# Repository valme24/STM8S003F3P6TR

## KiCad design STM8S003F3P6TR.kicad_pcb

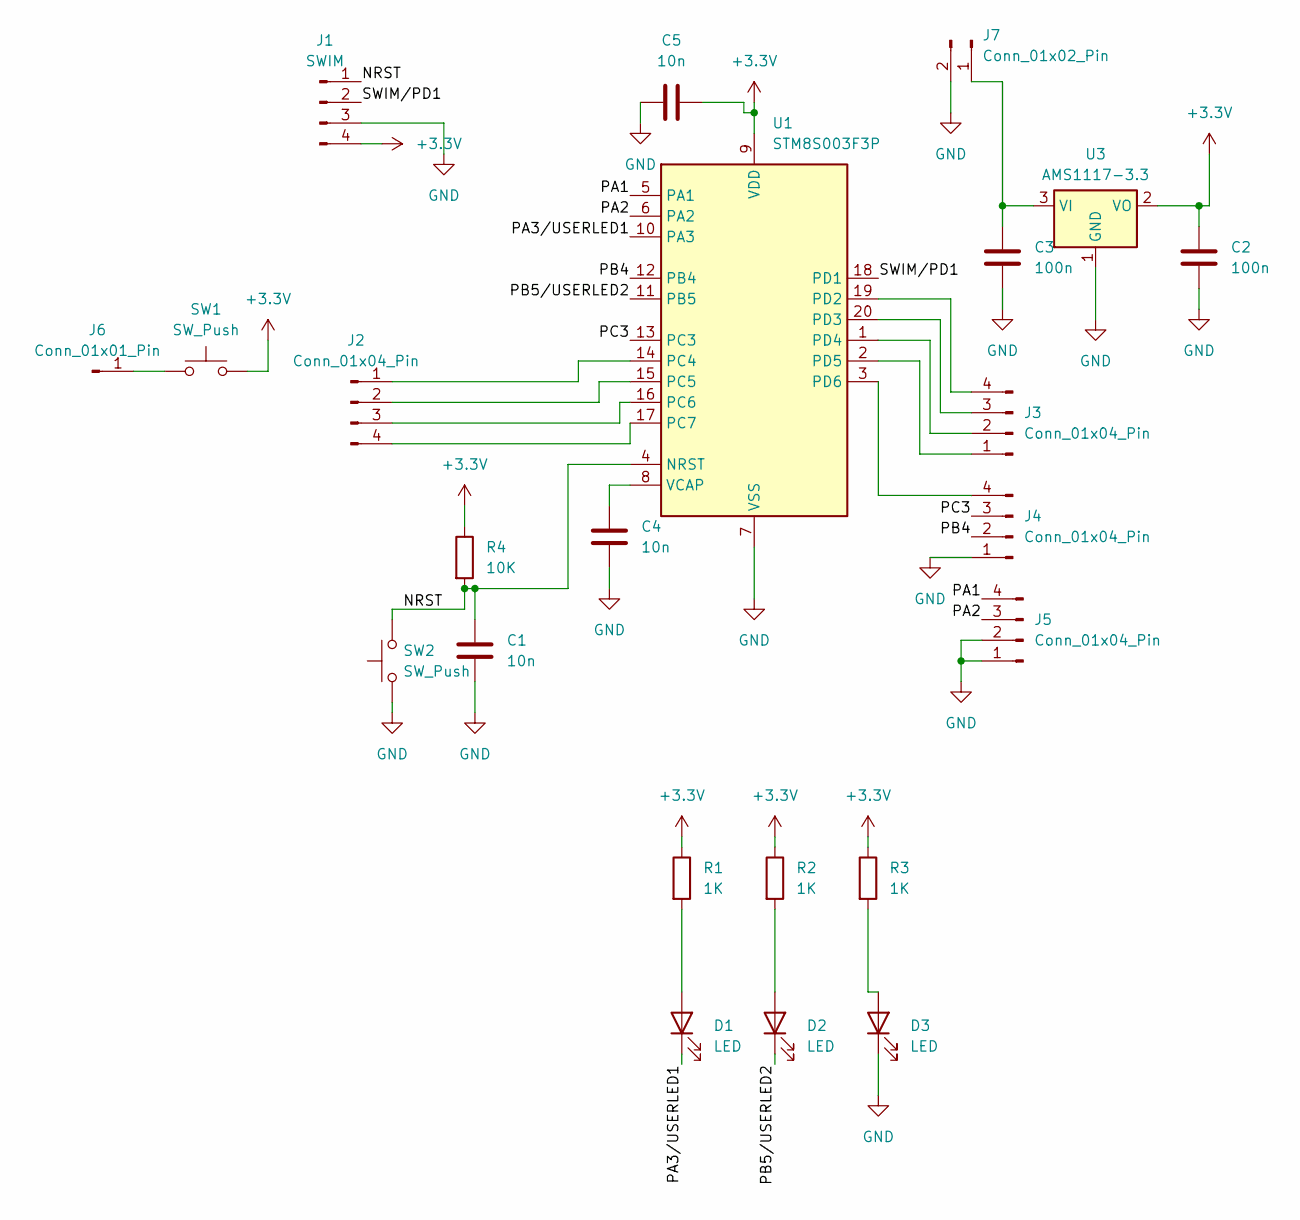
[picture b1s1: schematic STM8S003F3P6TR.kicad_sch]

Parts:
C1, C4, C5: 10n; C_0805_2012Metric
C2, C3: 100n; C_0805_2012Metric
D1, D2, D3: LED; LED_D3.0mm
J1: SWIM; PinHeader_1x04_P2.54mm_Vertical
J2, J3, J4, J5: Conn_01x04_Pin; PinHeader_1x04_P2.54mm_Vertical
J6: Conn_01x01_Pin; PinSocket_1x01_P2.54mm_Vertical
J7: Conn_01x02_Pin; CONN
R1, R2, R3: 1K; C_0603_1608Metric
R4: 10K; C_0603_1608Metric
SW1, SW2: SW_Push; SW_PUSH-12mm
U1: STM8S003F3P; TSSOP-20_4.4x6.5mm_P0.65mm
U3: AMS1117-3.3; SOT-223-3_TabPin2

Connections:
+3.3V: C2.1, C5.2, J1.4, R1.1, R2.1, R3.1, R4.1, SW1.2, U1.9 (VDD), U3.2 (VO); also elsewhere on the board
/NRST: C1.1, J1.1, R4.2, SW2.2, U1.4 (NRST); also elsewhere on the board
/PA1: J5.4, U1.5 (PA1)
/PA2: J5.3, U1.6 (PA2)
/PA3/USERLED1: D1.1 (K), U1.10 (PA3)
/PB4: J4.2, U1.12 (PB4)
/PB5/USERLED2: D2.1 (K), U1.11 (PB5)
/PC3: J4.3, U1.13 (PC3)
/SWIM/PD1: J1.2, U1.18 (PD1); also elsewhere on the board
GND: C1.2, C2.2, C3.2, C4.2, C5.1, D3.1 (K), J1.3, J4.1, J5.1, J5.2, J7.2, SW2.1, U1.7 (VSS), U3.1 (GND); also elsewhere on the board
unnamed: D1.2 (A), R1.2
unnamed: D2.2 (A), R2.2
unnamed: D3.2 (A), R3.2
unnamed: J2.1, U1.14 (PC4)
unnamed: J2.2, U1.15 (PC5)
unnamed: J2.3, U1.16 (PC6)
unnamed: J2.4, U1.17 (PC7)
unnamed: J3.1, U1.2 (PD5)
unnamed: J3.2, U1.1 (PD4)
unnamed: J3.3, U1.20 (PD3)
unnamed: J3.4, U1.19 (PD2)
unnamed: J4.4, U1.3 (PD6)
unnamed: J6.1 (Pin_1_1), SW1.1
unnamed: C3.1, J7.1, U3.3 (VI)
unnamed: C4.1, U1.8 (VCAP)

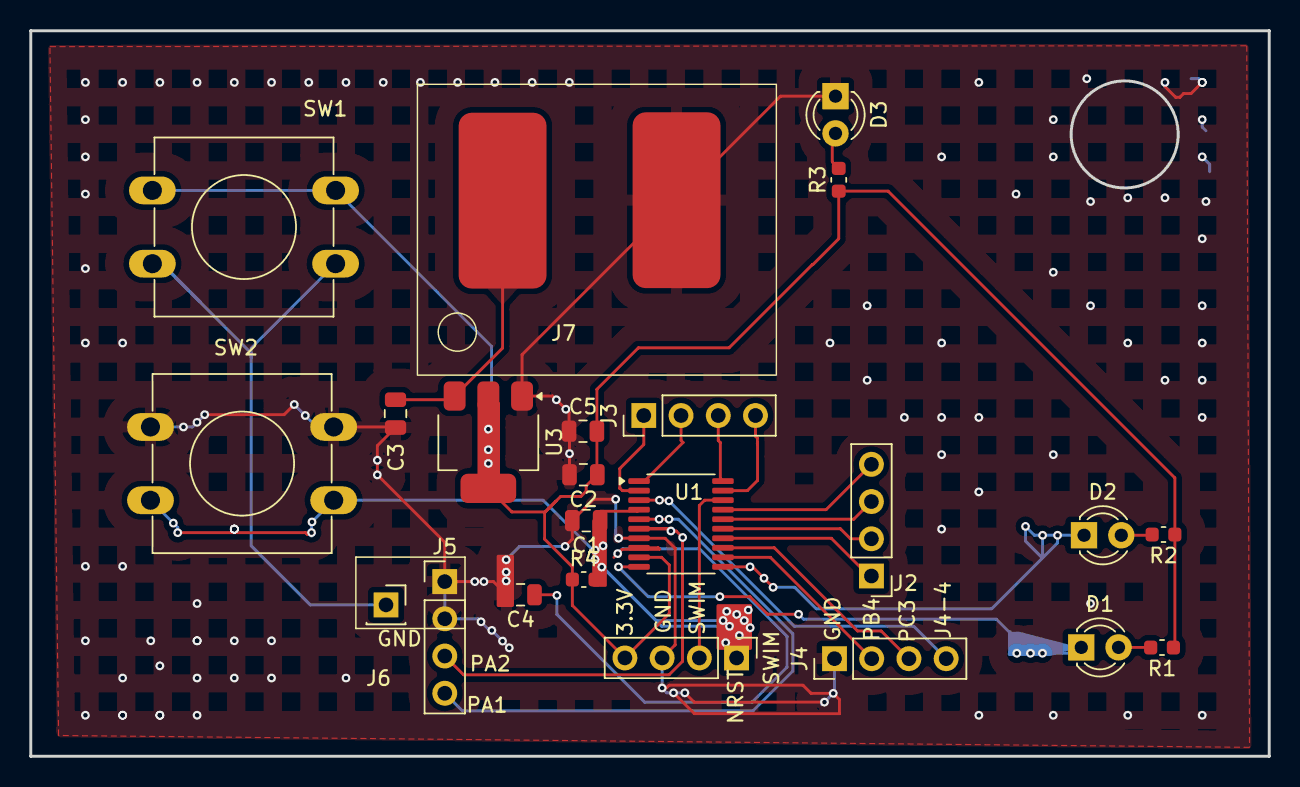
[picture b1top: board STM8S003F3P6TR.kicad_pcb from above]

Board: 2 copper layers, 84.5 x 49.5 mm, 23 parts (0 on the bottom side), 25 nets.

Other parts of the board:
SWIM : SWIM; PinHeader_1x04_P2.54mm_Vertical

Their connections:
+3.3V: SWIM.4; also elsewhere on the board
/NRST: SWIM.1; also elsewhere on the board
/SWIM/PD1: SWIM.2; also elsewhere on the board
GND: SWIM.3; also elsewhere on the board
